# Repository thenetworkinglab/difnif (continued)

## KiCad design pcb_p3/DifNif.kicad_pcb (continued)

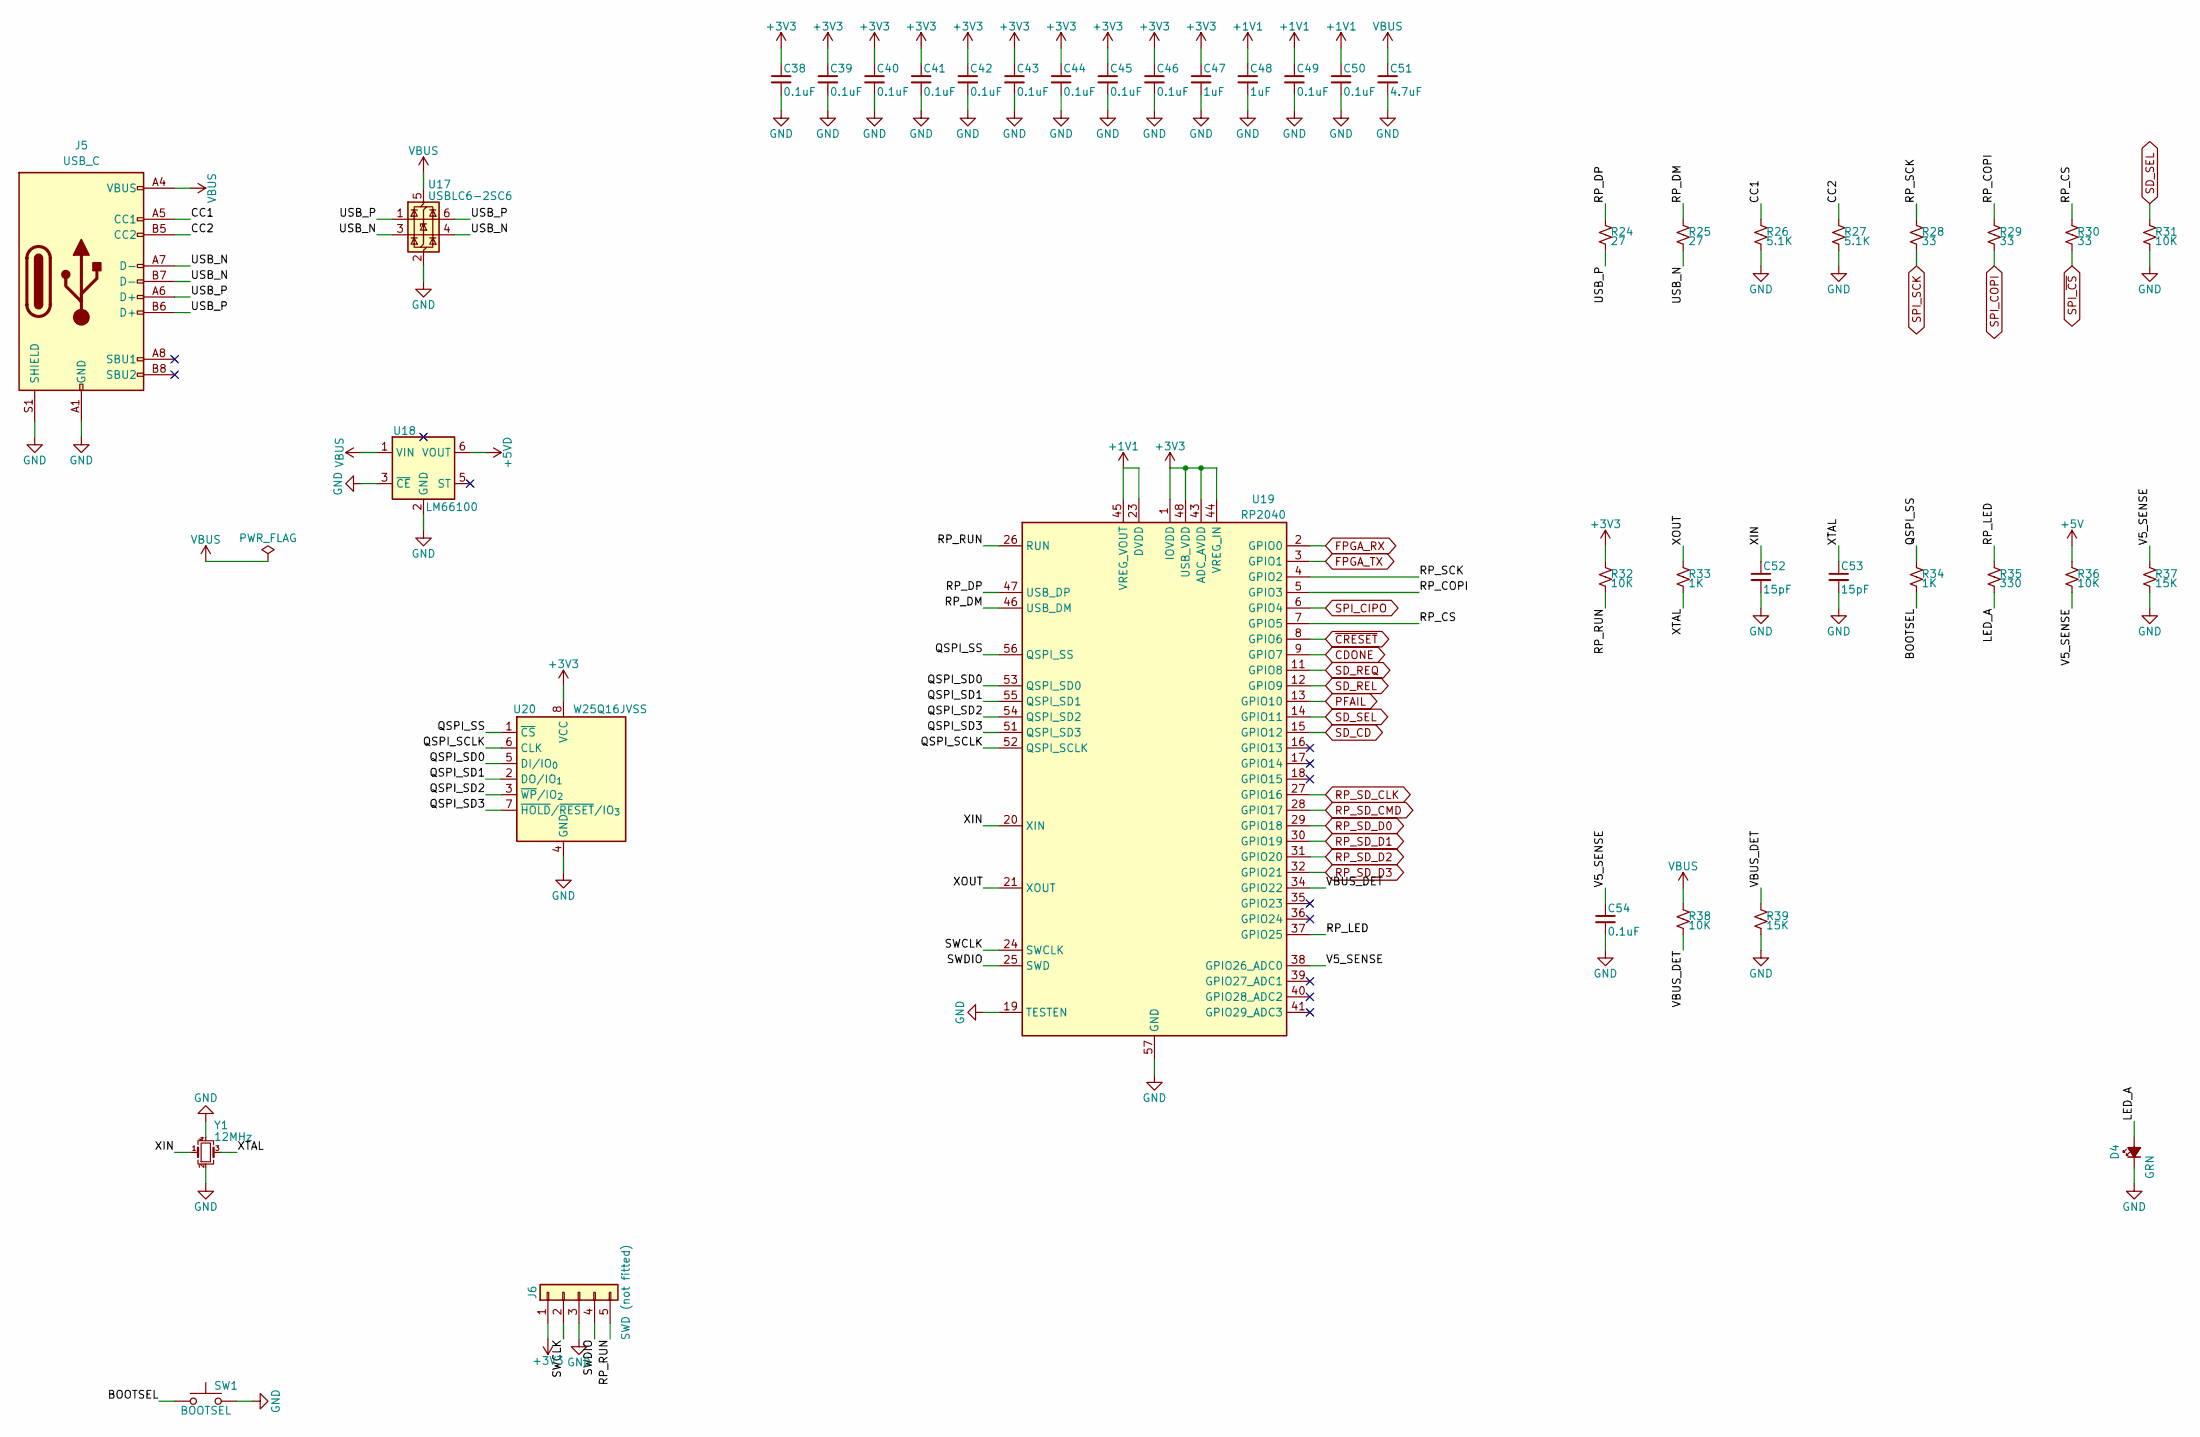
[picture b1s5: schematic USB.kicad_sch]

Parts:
C38, C39, C40, C41, C42, C43, C44, C45, C46, C49, C50, C54: 0.1uF; C_0603_1608Metric
C47, C48: 1uF; C_0603_1608Metric
C51: 4.7uF; C_0805_2012Metric
C52, C53: 15pF; C_0603_1608Metric
D4: GRN; LED_0603_1608Metric
J5: USB_C; USB_C_Receptacle_HRO_TYPE-C-31-M-12; MPN TYPE-C-31-M-12
J6: SWD (not fitted); PinHeader_1x05_P2.54mm_Vertical
R24, R25: 27; R_0603_1608Metric
R26, R27: 5.1K; R_0603_1608Metric
R28, R29, R30: 33; R_0603_1608Metric
R31, R32, R36, R38: 10K; R_0603_1608Metric
R33, R34: 1K; R_0603_1608Metric
R35: 330; R_0603_1608Metric
R37, R39: 15K; R_0603_1608Metric
SW1: BOOTSEL; SW_SPST_B3U-1000P; MPN B3U-1000P
U17: USBLC6-2SC6; SOT-23-6; MPN USBLC6-2SC6
U18: LM66100; SOT-363_SC-70-6; MPN LM66100DCKR
U19: RP2040; QFN-56-1EP_7x7mm_P0.4mm_EP3.2x3.2mm; MPN RP2040
U20: W25Q16JVSS; SOIC-8_5.3x5.3mm_P1.27mm; MPN W25Q16JVSSIQ
Y1: 12MHz; Crystal_SMD_3225-4Pin_3.2x2.5mm; MPN ABM8-272-T3

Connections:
+1V1: C48.1, C49.1, C50.1, U19.23 (DVDD), U19.45 (VREG_VOUT), U19.50 (DVDD)
+3V3: C38.1, C39.1, C40.1, C41.1, C42.1, C43.1, C44.1, C45.1, C46.1, C47.1, J6.1, R32.1, U19.1 (IOVDD), U19.10 (IOVDD), U19.22 (IOVDD), U19.33 (IOVDD), U19.42 (IOVDD), U19.43 (ADC_AVDD), U19.44 (VREG_IN), U19.48 (USB_VDD), U19.49 (IOVDD), U20.8 (VCC); also elsewhere on the board
+5V: R36.1; also elsewhere on the board
+5VD: U18.6 (VOUT); also elsewhere on the board
/USB/BOOTSEL: R34.2, SW1.1
/USB/CC1: J5.A5 (CC1), R26.1
/USB/CC2: J5.B5 (CC2), R27.1
/USB/LED_A: D4.2 (A), R35.2
/USB/QSPI_SCLK: U19.52 (QSPI_SCLK), U20.6 (CLK)
/USB/QSPI_SD0: U19.53 (QSPI_SD0), U20.5 (DI/IO_{0})
/USB/QSPI_SD1: U19.55 (QSPI_SD1), U20.2 (DO/IO_{1})
/USB/QSPI_SD2: U19.54 (QSPI_SD2), U20.3 (~WP/IO_{2})
/USB/QSPI_SD3: U19.51 (QSPI_SD3), U20.7 (~HOLD/~RESET/IO_{3})
/USB/QSPI_SS: R34.1, U19.56 (QSPI_SS), U20.1 (~CS)
/USB/RP_COPI: R29.1, U19.5 (GPIO3)
/USB/RP_CS: R30.1, U19.7 (GPIO5)
/USB/RP_DM: R25.1, U19.46 (USB_DM)
/USB/RP_DP: R24.1, U19.47 (USB_DP)
/USB/RP_LED: R35.1, U19.37 (GPIO25)
/USB/RP_RUN: J6.5, R32.2, U19.26 (RUN)
/USB/RP_SCK: R28.1, U19.4 (GPIO2)
/USB/SWCLK: J6.2, U19.24 (SWCLK)
/USB/SWDIO: J6.4, U19.25 (SWD)
/USB/USB_N: J5.A7 (D-), J5.B7 (D-), R25.2, U17.3 (I/O2), U17.4 (I/O2)
/USB/USB_P: J5.A6 (D+), J5.B6 (D+), R24.2, U17.1 (I/O1), U17.6 (I/O1)
/USB/V5_SENSE: C54.1, R36.2, R37.1, U19.38 (GPIO26_ADC0)
/USB/VBUS_DET: R38.2, R39.1, U19.34 (GPIO22)
/USB/XIN: C52.1, U19.20 (XIN), Y1.1
/USB/XOUT: R33.1, U19.21 (XOUT)
/USB/XTAL: C53.1, R33.2, Y1.3
CDONE: U19.9 (GPIO7); also elsewhere on the board
FPGA_RX: U19.2 (GPIO0); also elsewhere on the board
FPGA_TX: U19.3 (GPIO1); also elsewhere on the board
GND: C38.2, C39.2, C40.2, C41.2, C42.2, C43.2, C44.2, C45.2, C46.2, C47.2, C48.2, C49.2, C50.2, C51.2, C52.2, C53.2, C54.2, D4.1 (K), J5.A1 (GND), J5.A12 (GND), J5.B1 (GND), J5.B12 (GND), J5.S1 (SHIELD), J6.3, R26.2, R27.2, R31.2, R37.2, R39.2, SW1.2, U17.2 (GND), U18.2 (GND), U18.3 (~CE), U19.19 (TESTEN), U19.57 (GND), U20.4 (GND), Y1.2, Y1.4; also elsewhere on the board
PFAIL: U19.13 (GPIO10); also elsewhere on the board
RP_SD_CLK: U19.27 (GPIO16); also elsewhere on the board
RP_SD_CMD: U19.28 (GPIO17); also elsewhere on the board
RP_SD_D0: U19.29 (GPIO18); also elsewhere on the board
RP_SD_D1: U19.30 (GPIO19); also elsewhere on the board
RP_SD_D2: U19.31 (GPIO20); also elsewhere on the board
RP_SD_D3: U19.32 (GPIO21); also elsewhere on the board
SD_CD: U19.15 (GPIO12); also elsewhere on the board
SD_REL: U19.12 (GPIO9); also elsewhere on the board
SD_REQ: U19.11 (GPIO8); also elsewhere on the board
SD_SEL: R31.1, U19.14 (GPIO11); also elsewhere on the board
SPI_CIPO: U19.6 (GPIO4); also elsewhere on the board
SPI_COPI: R29.2; also elsewhere on the board
SPI_SCK: R28.2; also elsewhere on the board
SPI_~CS: R30.2; also elsewhere on the board
VBUS: C51.1, J5.A4 (VBUS), J5.A9 (VBUS), J5.B4 (VBUS), J5.B9 (VBUS), R38.1, U17.5 (VBUS), U18.1 (VIN)
~CRESET: U19.8 (GPIO6); also elsewhere on the board

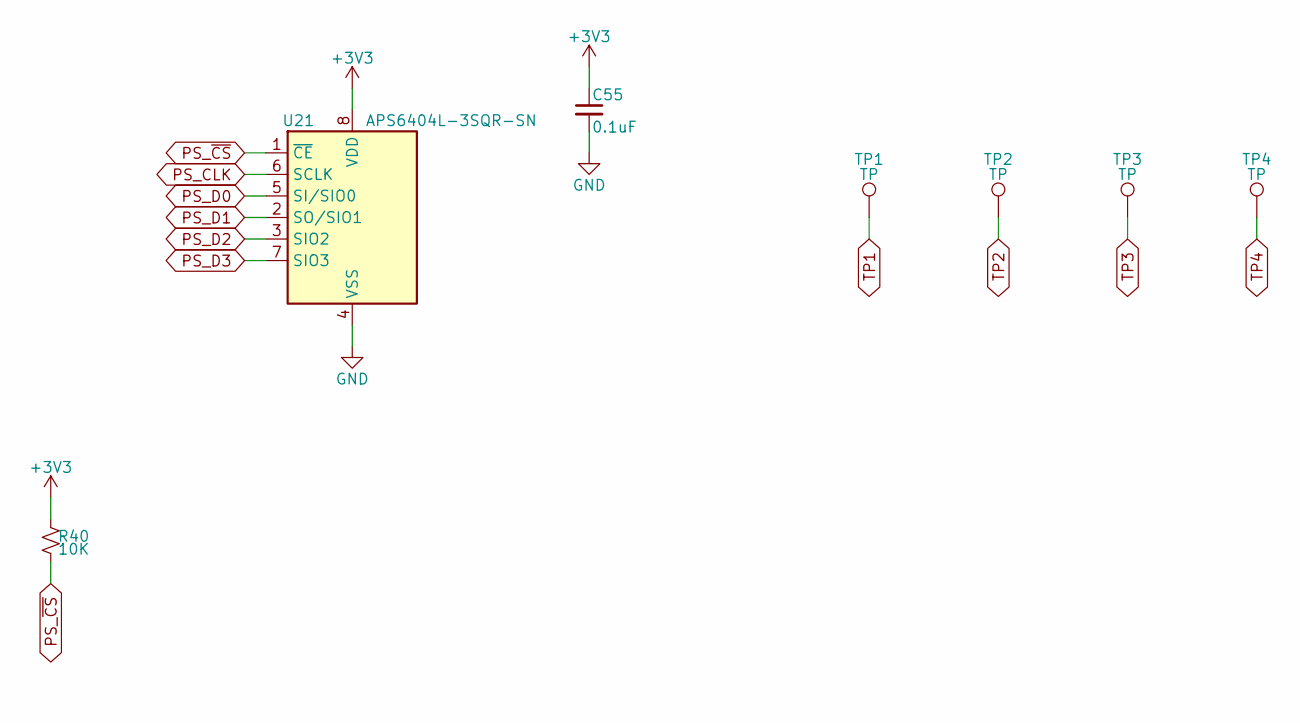
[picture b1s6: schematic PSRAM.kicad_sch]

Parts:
C55: 0.1uF; C_0603_1608Metric
R40: 10K; R_0603_1608Metric
TP1, TP2, TP3, TP4: TP; TestPoint_Pad_D1.5mm
U21: APS6404L-3SQR-SN; SOIC-8_3.9x4.9mm_P1.27mm; MPN APS6404L-3SQR-SN

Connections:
+3V3: C55.1, R40.1, U21.8 (VDD); also elsewhere on the board
GND: C55.2, U21.4 (VSS); also elsewhere on the board
PS_CLK: U21.6 (SCLK); also elsewhere on the board
PS_D0: U21.5 (SI/SIO0); also elsewhere on the board
PS_D1: U21.2 (SO/SIO1); also elsewhere on the board
PS_D2: U21.3 (SIO2); also elsewhere on the board
PS_D3: U21.7 (SIO3); also elsewhere on the board
PS_~CS: R40.2, U21.1 (~CE); also elsewhere on the board
TP1: TP1.1; also elsewhere on the board
TP2: TP2.1; also elsewhere on the board
TP3: TP3.1; also elsewhere on the board
TP4: TP4.1; also elsewhere on the board

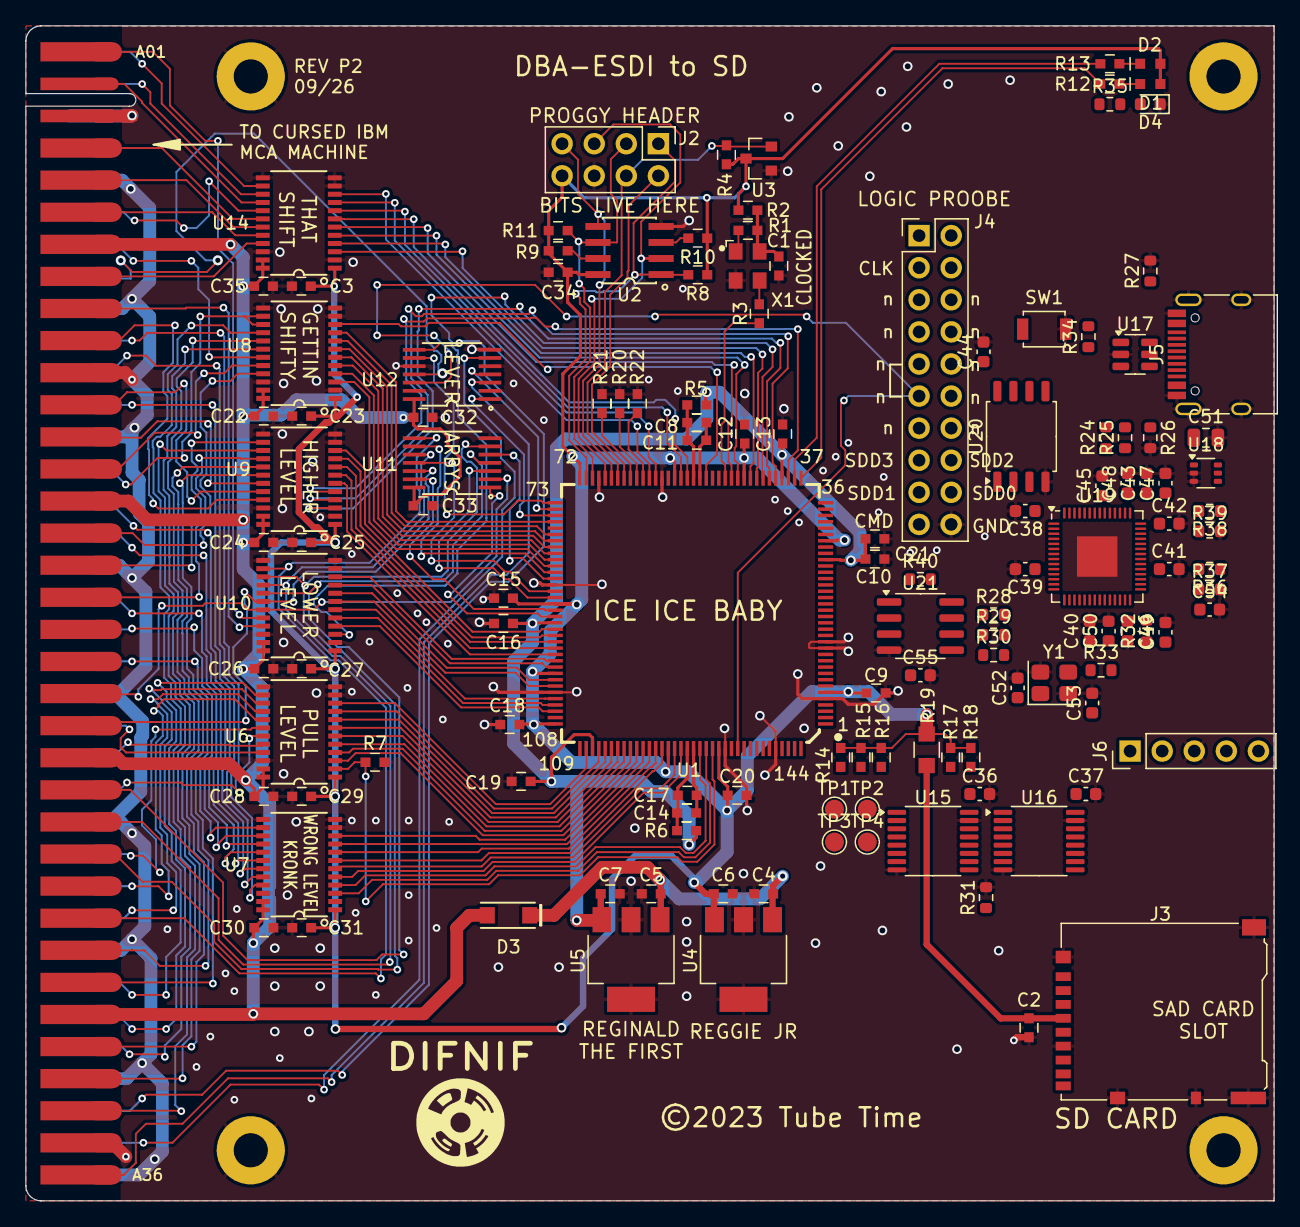
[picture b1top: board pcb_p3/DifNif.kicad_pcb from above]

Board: 2 copper layers, 98.8 x 93.0 mm, 135 parts (0 on the bottom side), 203 nets.

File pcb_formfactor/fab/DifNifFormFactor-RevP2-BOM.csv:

Item,Qty,Designators,Manufacturer,Manufacturer Part Number,Description,Value,Footprint,Type,Fitted by,Mouser,Notes
1,13,C1 C2 C9 C10 C11 C12 C13 C15 C16 C17 C18 C19 C34,TDK,CGA3E1X7R1C105AC,Capacitor 1u 0603,1u,CAPC1608X100,SMD,Assembler,810-CGA3E1X7R1C105AC,
2,14,C3 C22 C23 C24 C25 C26 C27 C28 C29 C30 C31 C32 C33 C35,Samsung Electro-Mechanics,CL10B104KB8NNNC,Capacitor 0.1uF 0603,0.1uF,CAPC1608X100,SMD,Assembler,,Any 0.1 uF X7R 0603 rated 16 V or more is fine
3,8,C4 C5 C6 C7 C8 C14 C20 C21,Samsung Electro-Mechanics,CL10A475KP8NNNC,Capacitor 4.7u 0603,4.7u,CAPC1608X100,SMD,Assembler,187-CL10A475KP8NNNC,
4,2,D1 D2,,,"LED, 0603",LED,LEDM1608X50,SMD,Assembler,,Any 0603 LED (e.g. green); 470 ohm from 3.3 V
5,1,D3,Nexperia,PMEG10010ELRX,"Schottky diode 1 A 100 V, SOD-123F",PMEG10010ELR,SOD3716X117,SMD,Assembler,771-PMEG10010ELRX,
6,1,J3,Hirose,DM3AT-SF-PEJM5(40),microSD socket,SDCARD_DM3AT-SF-PEJM5,microSD_HC_Hirose_DM3AT-SF-PEJM5,SMD,Assembler,798-DM3AT-SF-PEJM540,"Check: Mouser code ends in 40, Hirose's packaging variant"
7,6,R1 R4 R8 R9 R10 R11,Yageo,RC0603FR-0710KL,Resistor 10K 0603,10K,RESC1608X55,SMD,Assembler,603-RC0603FR-0710KL,
8,6,R2 R3 R20 R21 R22 R23,Yageo,RC0603FR-0710RL,Resistor 10 0603,10,RESC1608X55,SMD,Assembler,603-RC0603FR-0710RL,
9,2,R5 R6,Yageo,RC0603FR-07100RL,Resistor 100 0603,100,RESC1608X55,SMD,Assembler,603-RC0603FR-07100RL,
10,1,R7,Yageo,RC0603FR-071KL,Resistor 1K 0603,1K,RESC1608X55,SMD,Assembler,603-RC0603FR-071KL,
11,2,R12 R13,Yageo,RC0603FR-07470RL,Resistor 470 0603,470,RESC1608X55,SMD,Assembler,603-RC0603FR-07470RL,
12,5,R14 R15 R16 R17 R18,Yageo,RC0603FR-0747KL,Resistor 47K 0603,47K,RESC1608X55,SMD,Assembler,603-RC0603FR-0747KL,
13,1,R19,Yageo,RC0805FR-070RL,Resistor 0 0805,0,RESC2012X55,SMD,Assembler,603-RC0805FR-070RL,
14,1,U1,Lattice Semiconductor,ICE40HX4K-TQ144,"FPGA, iCE40 HX4K, TQFP-144",ICE40HX4K-TQ144,TSQFP50P2200X2200X160-144,SMD,Assembler,842-ICE40HX4K-TQ144,
15,1,U2,Microchip Technology,SST26VF080A-104I/SN,"SPI flash 8 Mbit, SOIC-8 (FPGA configuration)",SST26VF080A-104I/SN,SOP127P620X175-8,SMD,Assembler,579-26VF080A-104I/SN,
16,1,U3,Diodes Incorporated,APX803S00-29SA-7,"Reset supervisor 2.93 V, SOT-23",APX803S00-29SA-7,SOT95P230X117-3,SMD,Assembler,621-APX803S00-29SA-7,
17,1,U4,Diodes Incorporated,AP2114HA-3.3TRG1,"LDO 3.3 V, SOT-223",AP2114HA-3.3,SOT230P700X170-3,SMD,Assembler,621-AP2114HA-3.3TRG1,
18,1,U5,Diodes Incorporated,AP2114HA-1.2TRG1,"LDO 1.2 V, SOT-223",AP2114HA-1.2,SOT230P700X170-3,SMD,Assembler,621-AP2114HA-1.2TRG1,
19,6,U6 U7 U8 U9 U10 U14,Texas Instruments,SN74LVC8T245PWR,"Dual-supply octal transceiver, TSSOP-24",74LVC8T245,TSOP65P640X120-24,SMD,Assembler,595-SN74LVC8T245PWR,
20,1,U11,Toshiba,74LCX07FT,"Hex open-drain buffer, TSSOP-14",74LCX07,TSOP65P640X110-14,SMD,Assembler,757-74LCX07FTAE,Check: Mouser code adds a packaging suffix (AE)
21,1,U12,Toshiba,74VHCT125AFT,"Quad tri-state buffer, TSSOP-14",74VHCT125,TSOP65P640X110-14,SMD,Assembler,757-74VHCT125AFT,
22,1,X1,ECS Inc.,ECS-2333-100-BN-TR,Oscillator 10 MHz,ASE-xxxMHz,XTAL320X250X120-4,SMD,Assembler,520-ECS-2333-100-BNT,"Check: 10 MHz 3.3 V oscillator, 3.2 x 2.5 mm; Mouser code drops the -TR punctuation"
23,1,J2,,,"2x4 pin header, 2.54 mm",PROG,PinHeader_2x04_P2.54mm_Vertical,THT,Customer,,FPGA flash programming header
24,1,J4,,,"2x10 pin header, 2.54 mm",HPLA_PORT,PinHeader_2x10_P2.54mm_Vertical,THT,Customer,,Logic analyzer header (HP pod)
25,1,U13,,,"2x 1x24 female socket strips, 2.54 mm, rows 15.24 mm apart",Teensy4_1,DIP-48_W15.24mm_Socket,THT,Customer,,Socket for the Teensy 4.1 (Teensy fitted separately)

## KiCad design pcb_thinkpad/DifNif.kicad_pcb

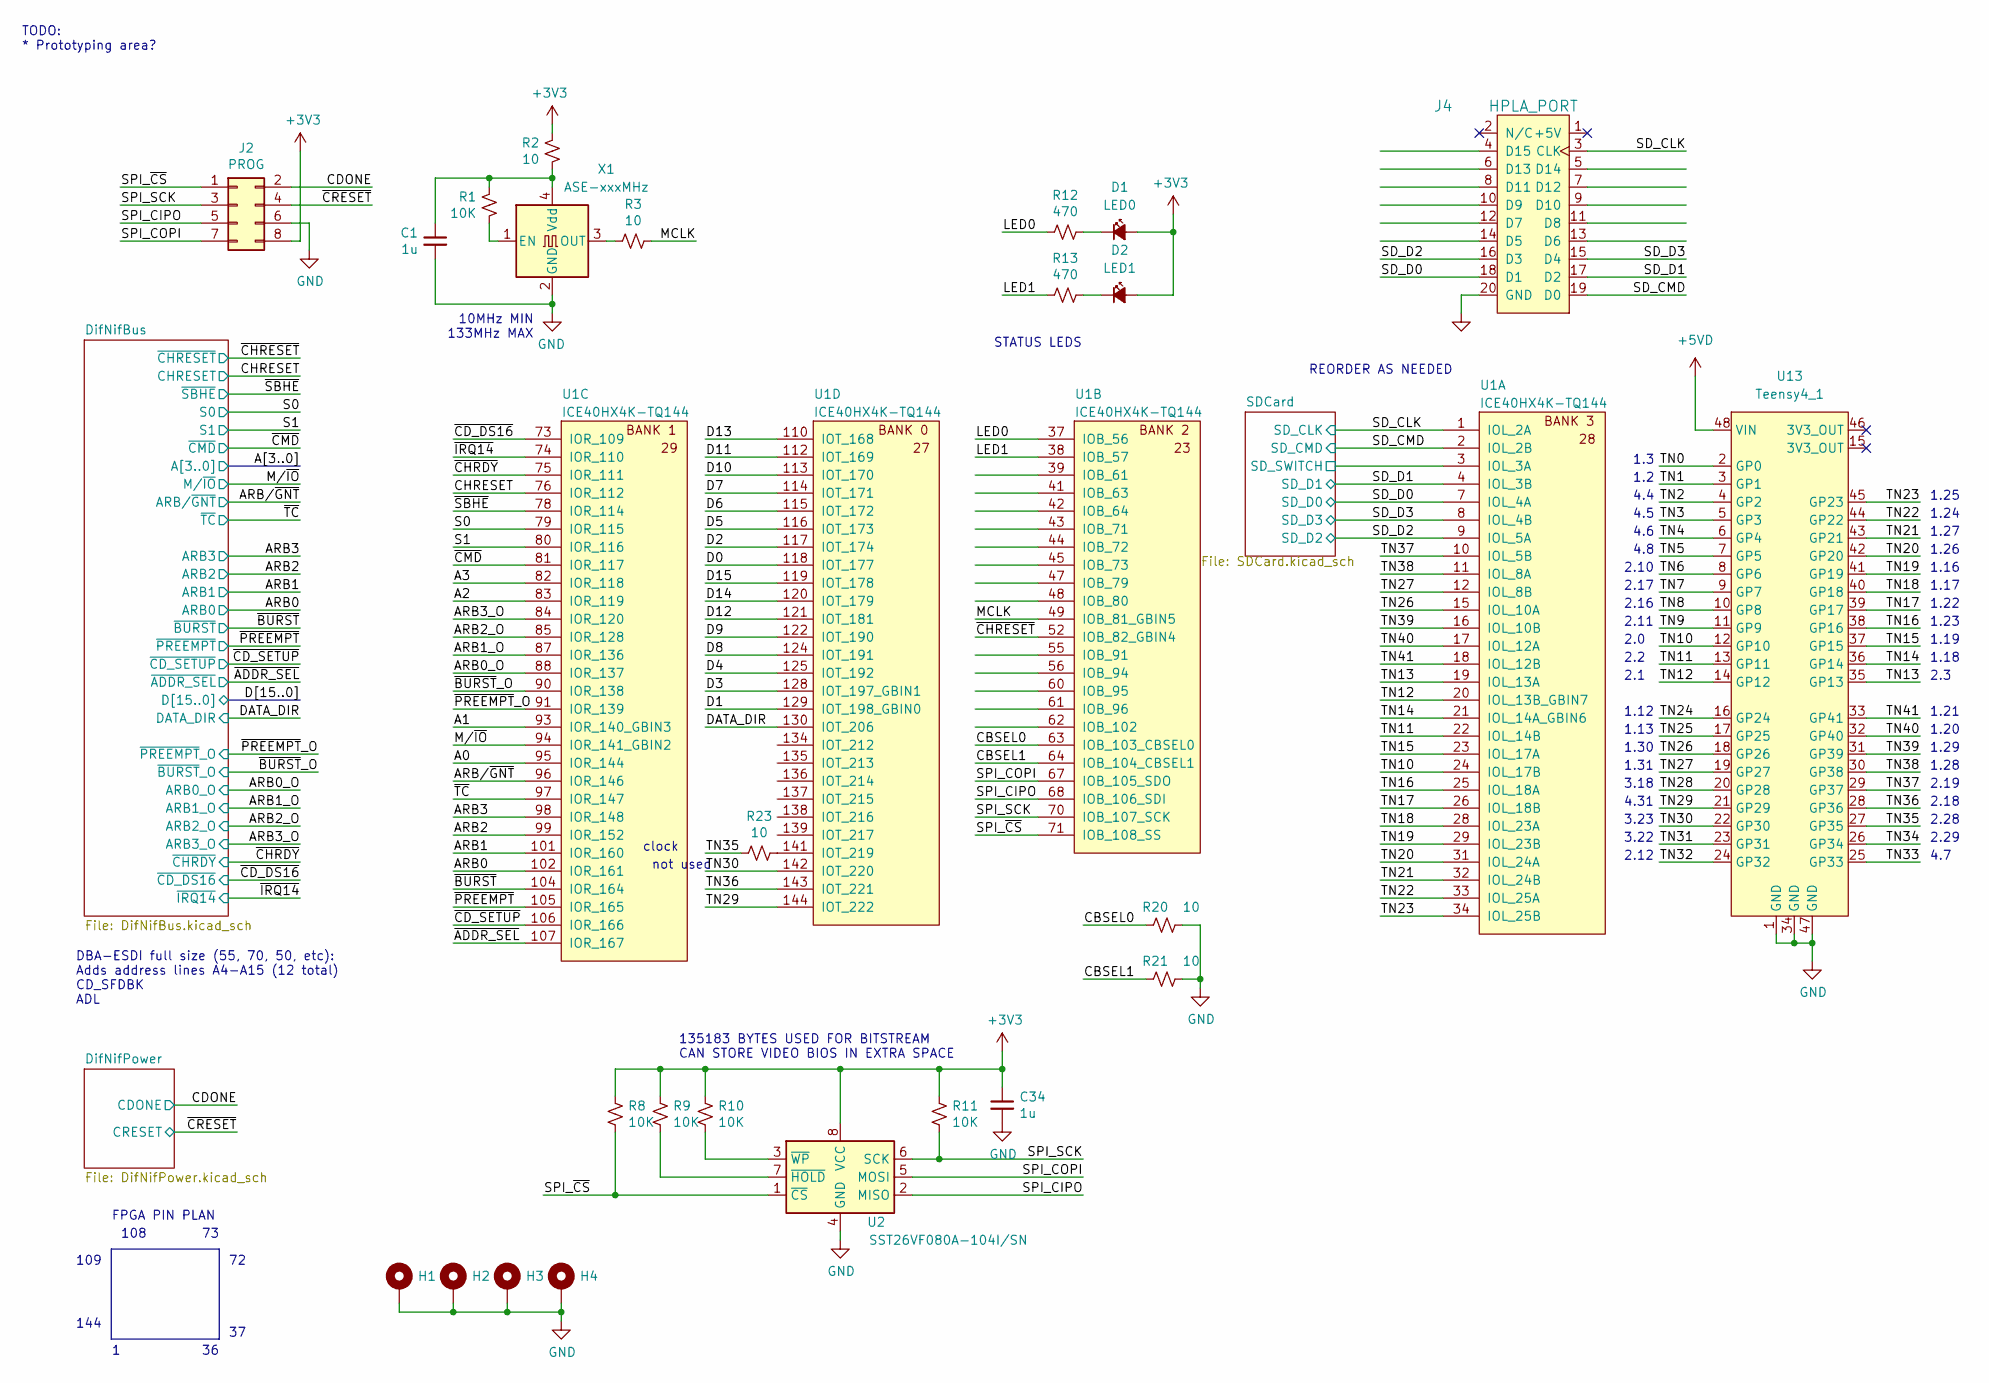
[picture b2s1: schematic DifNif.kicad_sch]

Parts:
C1, C34: 1u; CAPC1608X100; Mouser 810-CGA3E1X7R1C105AC
D1: LED0; LEDM1608X50
D2: LED1; LEDM1608X50
H1, H2, H3, H4: MountingHole_Pad; MountingHole_2.7mm_Pad
J2: PROG; PinHeader_2x04_P2.54mm_Vertical
J4: HPLA_PORT; PinHeader_2x10_P2.54mm_Vertical
R1, R8, R9, R10, R11: 10K; RESC1608X55; Mouser 603-RC0603FR-0710KL
R2, R3, R20, R21, R23: 10; RESC1608X55; Mouser 603-RC0603FR-0710RL
R12, R13: 470; RESC1608X55; Mouser 603-RC0603FR-07470RL
U1: ICE40HX4K-TQ144; TSQFP50P2200X2200X160-144; Mouser 842-ICE40HX4K-TQ144
U2: SST26VF080A-104I/SN; SOP127P620X175-8; Mouser 579-26VF080A-104I/SN
U13: Teensy4_1; DIP-48_W15.24mm_Socket
X1: ASE-xxxMHz; XTAL320X250X120-4; Mouser 520-ECS-2333-100-BNT

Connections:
+3V3: C34.1, D1.2 (A), D2.2 (A), J2.8, R2.1, R8.1, R9.1, R10.1, R11.1, U2.8 (VCC); also elsewhere on the board
+5VD: U13.48 (VIN); also elsewhere on the board
/A0: U1.95 (IOR_144); also elsewhere on the board
/A1: U1.93 (IOR_140_GBIN3); also elsewhere on the board
/A2: U1.83 (IOR_119); also elsewhere on the board
/A3: U1.82 (IOR_118); also elsewhere on the board
/ARB0: U1.102 (IOR_161); also elsewhere on the board
/ARB0_O: U1.88 (IOR_137); also elsewhere on the board
/ARB1: U1.101 (IOR_160); also elsewhere on the board
/ARB1_O: U1.87 (IOR_136); also elsewhere on the board
/ARB2: U1.99 (IOR_152); also elsewhere on the board
/ARB2_O: U1.85 (IOR_128); also elsewhere on the board
/ARB3: U1.98 (IOR_148); also elsewhere on the board
/ARB3_O: U1.84 (IOR_120); also elsewhere on the board
/ARB/~GNT: U1.96 (IOR_146); also elsewhere on the board
/CBSEL0: R20.2, U1.63 (IOB_103_CBSEL0)
/CBSEL1: R21.2, U1.64 (IOB_104_CBSEL1)
/CDONE: J2.2; also elsewhere on the board
/CHRESET: U1.76 (IOR_112); also elsewhere on the board
/D0: U1.118 (IOT_177); also elsewhere on the board
/D1: U1.129 (IOT_198_GBIN0); also elsewhere on the board
/D2: U1.117 (IOT_174); also elsewhere on the board
/D3: U1.128 (IOT_197_GBIN1); also elsewhere on the board
/D4: U1.125 (IOT_192); also elsewhere on the board
/D5: U1.116 (IOT_173); also elsewhere on the board
/D6: U1.115 (IOT_172); also elsewhere on the board
/D7: U1.114 (IOT_171); also elsewhere on the board
/D8: U1.124 (IOT_191); also elsewhere on the board
/D9: U1.122 (IOT_190); also elsewhere on the board
/D10: U1.113 (IOT_170); also elsewhere on the board
/D11: U1.112 (IOT_169); also elsewhere on the board
/D12: U1.121 (IOT_181); also elsewhere on the board
/D13: U1.110 (IOT_168); also elsewhere on the board
/D14: U1.120 (IOT_179); also elsewhere on the board
/D15: U1.119 (IOT_178); also elsewhere on the board
/DATA_DIR: U1.130 (IOT_206); also elsewhere on the board
/LED0: R12.2, U1.37 (IOB_56)
/LED1: R13.2, U1.38 (IOB_57)
/MCLK: R3.1, U1.49 (IOB_81_GBIN5)
/M/~IO: U1.94 (IOR_141_GBIN2); also elsewhere on the board
/S0: U1.79 (IOR_115); also elsewhere on the board
/S1: U1.80 (IOR_116); also elsewhere on the board
/SDCard/SD_SWITCH: U1.3 (IOL_3A); also elsewhere on the board
/SD_CLK: J4.3 (CLK), U1.1 (IOL_2A); also elsewhere on the board
/SD_CMD: J4.19 (D0), U1.2 (IOL_2B); also elsewhere on the board
/SD_D0: J4.18 (D1), U1.7 (IOL_4A); also elsewhere on the board
/SD_D1: J4.17 (D2), U1.4 (IOL_3B); also elsewhere on the board
/SD_D2: J4.16 (D3), U1.9 (IOL_5A); also elsewhere on the board
/SD_D3: J4.15 (D4), U1.8 (IOL_4B); also elsewhere on the board
/SPI_CIPO: J2.5, U1.68 (IOB_106_SDI), U2.2 (MISO)
/SPI_COPI: J2.7, U1.67 (IOB_105_SDO), U2.5 (MOSI)
/SPI_SCK: J2.3, R11.2, U1.70 (IOB_107_SCK), U2.6 (SCK)
/SPI_~CS: J2.1, R8.2, U1.71 (IOB_108_SS), U2.1 (~CS)
/TN0: U13.2 (GP0)
/TN1: U13.3 (GP1)
/TN2: U13.4 (GP2)
/TN3: U13.5 (GP3)
/TN4: U13.6 (GP4)
/TN5: U13.7 (GP5)
/TN6: U13.8 (GP6)
/TN7: U13.9 (GP7)
/TN8: U13.10 (GP8)
/TN9: U13.11 (GP9)
/TN10: U1.24 (IOL_17B), U13.12 (GP10)
/TN11: U1.22 (IOL_14B), U13.13 (GP11)
/TN12: U1.20 (IOL_13B_GBIN7), U13.14 (GP12)
/TN13: U1.19 (IOL_13A), U13.35 (GP13)
/TN14: U1.21 (IOL_14A_GBIN6), U13.36 (GP14)
/TN15: U1.23 (IOL_17A), U13.37 (GP15)
/TN16: U1.25 (IOL_18A), U13.38 (GP16)
/TN17: U1.26 (IOL_18B), U13.39 (GP17)
/TN18: U1.28 (IOL_23A), U13.40 (GP18)
/TN19: U1.29 (IOL_23B), U13.41 (GP19)
/TN20: U1.31 (IOL_24A), U13.42 (GP20)
/TN21: U1.32 (IOL_24B), U13.43 (GP21)
/TN22: U1.33 (IOL_25A), U13.44 (GP22)
/TN23: U1.34 (IOL_25B), U13.45 (GP23)
/TN24: U13.16 (GP24)
/TN25: U13.17 (GP25)
/TN26: U1.15 (IOL_10A), U13.18 (GP26)
/TN27: U1.12 (IOL_8B), U13.19 (GP27)
/TN28: U13.20 (GP28)
/TN29: U1.144 (IOT_222), U13.21 (GP29)
/TN30: U1.142 (IOT_220), U13.22 (GP30)
/TN31: U13.23 (GP31)
/TN32: U13.24 (GP32)
/TN33: U13.25 (GP33)
/TN34: U13.26 (GP34)
/TN35: R23.2, U13.27 (GP35)
/TN36: U1.143 (IOT_221), U13.28 (GP36)
/TN37: U1.10 (IOL_5B), U13.29 (GP37)
/TN38: U1.11 (IOL_8A), U13.30 (GP38)
/TN39: U1.16 (IOL_10B), U13.31 (GP39)
/TN40: U1.17 (IOL_12A), U13.32 (GP40)
/TN41: U1.18 (IOL_12B), U13.33 (GP41)
/~ADDR_SEL: U1.107 (IOR_167); also elsewhere on the board
/~BURST: U1.104 (IOR_164); also elsewhere on the board
/~BURST_O: U1.90 (IOR_138); also elsewhere on the board
/~CD_DS16: U1.73 (IOR_109); also elsewhere on the board
/~CD_SETUP: U1.106 (IOR_166); also elsewhere on the board
/~CHRDY: U1.75 (IOR_111); also elsewhere on the board
/~CHRESET: U1.52 (IOB_82_GBIN4); also elsewhere on the board
/~CMD: U1.81 (IOR_117); also elsewhere on the board
/~CRESET: J2.4; also elsewhere on the board
/~IRQ14: U1.74 (IOR_110); also elsewhere on the board
/~PREEMPT: U1.105 (IOR_165); also elsewhere on the board
/~PREEMPT_O: U1.91 (IOR_139); also elsewhere on the board
/~SBHE: U1.78 (IOR_114); also elsewhere on the board
/~TC: U1.97 (IOR_147); also elsewhere on the board
GND: C1.2, C34.2, H1.1, H2.1, H3.1, H4.1, J2.6, J4.20 (GND), R20.1, R21.1, U2.4 (GND), U13.1 (GND), U13.34 (GND), U13.47 (GND), X1.2 (GND); also elsewhere on the board
unnamed: C1.1, R1.1, R2.2, X1.4 (Vdd)
unnamed: D1.1 (K), R12.1
unnamed: D2.1 (K), R13.1
unnamed: R1.2, X1.1 (EN)
unnamed: R3.2, X1.3 (OUT)
unnamed: R9.2, U2.7 (~HOLD)
unnamed: R10.2, U2.3 (~WP)
unnamed: R23.1, U1.141 (IOT_219)

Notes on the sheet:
2.1
2.19
4.31
1.16
2.17
2.18
1.30
2.16
1.27
clock
1.2
REORDER AS NEEDED
2.3
2.0
3.22
STATUS LEDS
TODO: * Prototyping area?
4.7
1.31
1.21
2.28
1.24
1.29
1.19
4.6
2.12
2.10
3.18
1.17
3.23
1.3
1.25
4.5
1.20
2.29
2.11
4.4
135183 BYTES USED FOR BITSTREAM CAN STORE VIDEO BIOS IN EXTRA SPACE
1.18
1.28
